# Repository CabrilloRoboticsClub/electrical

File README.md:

# MATE ROV Electrical Stack for 2024 ROV Seahawk II

## Overview
This year, we decided to develop a stack of custom boards for the first time. We made this decision to reduce the size and weight of the Seahawk II while also improving overall durability, reliability, and power consumption. In the past, wiring harnesses were a significant point of failure, so we aimed to reduce their use.

## Intorduction

The Seahawk II electrical stack focuses on high integration. We reduced the number of boards to three, which all connect seamlessly. This minimized space requirements. While the R&D expenses for developing these boards were high, the completed stack is incredibly reliable and significantly reduces costs compared to off-the-shelf options.

## For exstive documetaion go to the wiki

https://github.com/CabrilloRoboticsClub/electrical/wiki

### Members of 2024 electrical team:
- Isaac Wax
- Isaac Eda

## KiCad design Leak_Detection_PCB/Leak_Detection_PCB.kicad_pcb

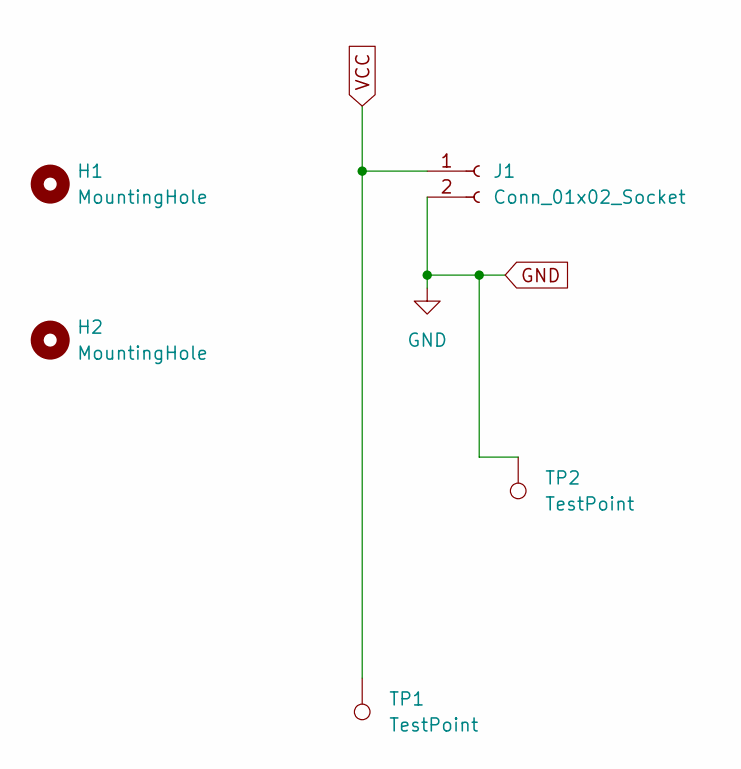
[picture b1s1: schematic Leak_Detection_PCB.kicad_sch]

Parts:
H1, H2: MountingHole; MountingHole_2.2mm_M2_Pad
J1: Conn_01x02_Socket; PinHeader_1x02_P2.54mm_Vertical_SMD_Pin1Left
TP1, TP2: TestPoint; TestPoint_Pad_D1.5mm

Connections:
GND: J1.2, TP2.1
VCC: J1.1, TP1.1

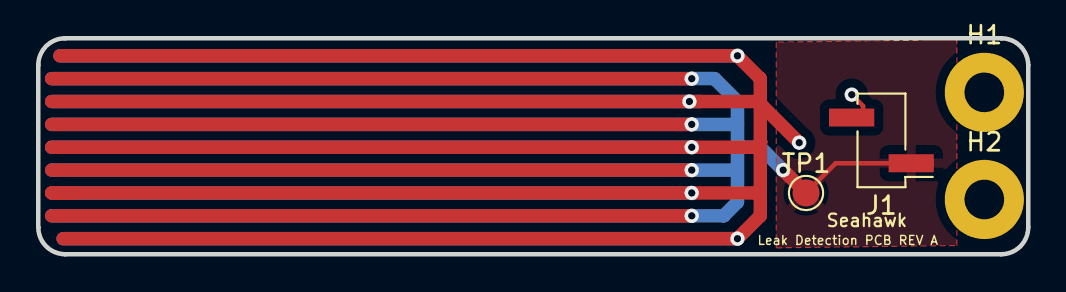
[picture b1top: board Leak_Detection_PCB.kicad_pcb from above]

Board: 2 copper layers, 55.0 x 12.0 mm, 5 parts (1 on the bottom side), 2 nets.

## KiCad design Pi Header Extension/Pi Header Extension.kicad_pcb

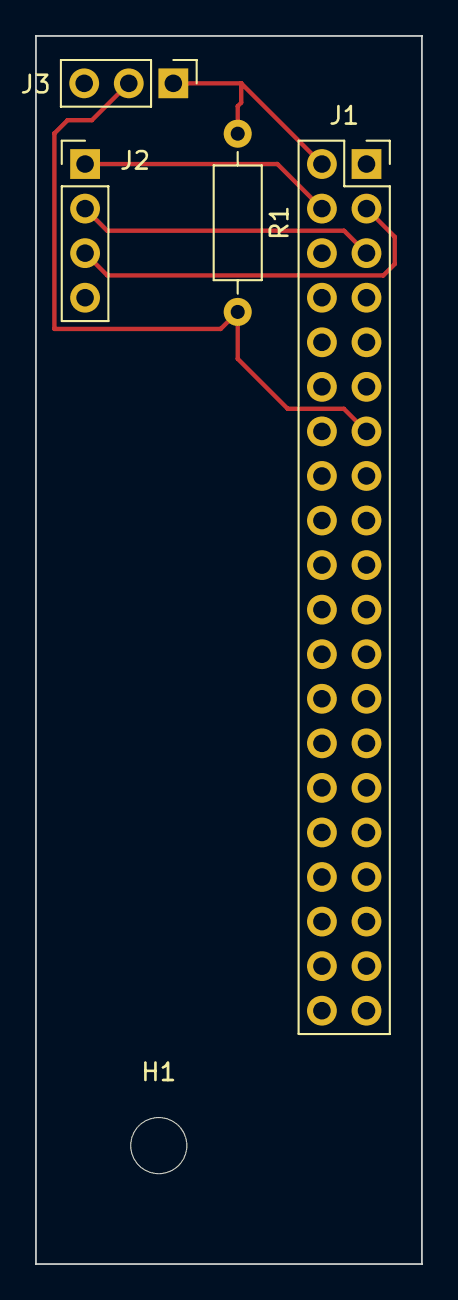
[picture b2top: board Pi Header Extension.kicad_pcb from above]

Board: 2 copper layers, 22.0 x 70.0 mm, 5 parts (0 on the bottom side), 6 nets.

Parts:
H1: MountingHole; MountingHole_3.2mm_M3
J1: Conn_02x20_Odd_Even; PinSocket_2x20_P2.54mm_Vertical
J2: Conn_01x04_Pin; PinHeader_1x04_P2.54mm_Vertical
J3: Conn_01x03_Pin; PinHeader_1x03_P2.54mm_Vertical
R1: 4.7k; R_Axial_DIN0207_L6.3mm_D2.5mm_P10.16mm_Horizontal

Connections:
/5V: J1.2, J3.1, R1.1
/GND: J1.6, J1.14, J2.4, J3.3
/GPIO: J1.13, J3.2, R1.2
/SCL: J1.5, J2.2
/SDA: J1.3, J2.3
/Vin: J1.4, J2.1

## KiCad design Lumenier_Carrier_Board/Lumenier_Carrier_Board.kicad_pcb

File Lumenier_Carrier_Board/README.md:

# Lumenier ESC Carrier Board
https://github.com/CabrilloRoboticsClub/electrical/wiki/ESC-Carrier-Board

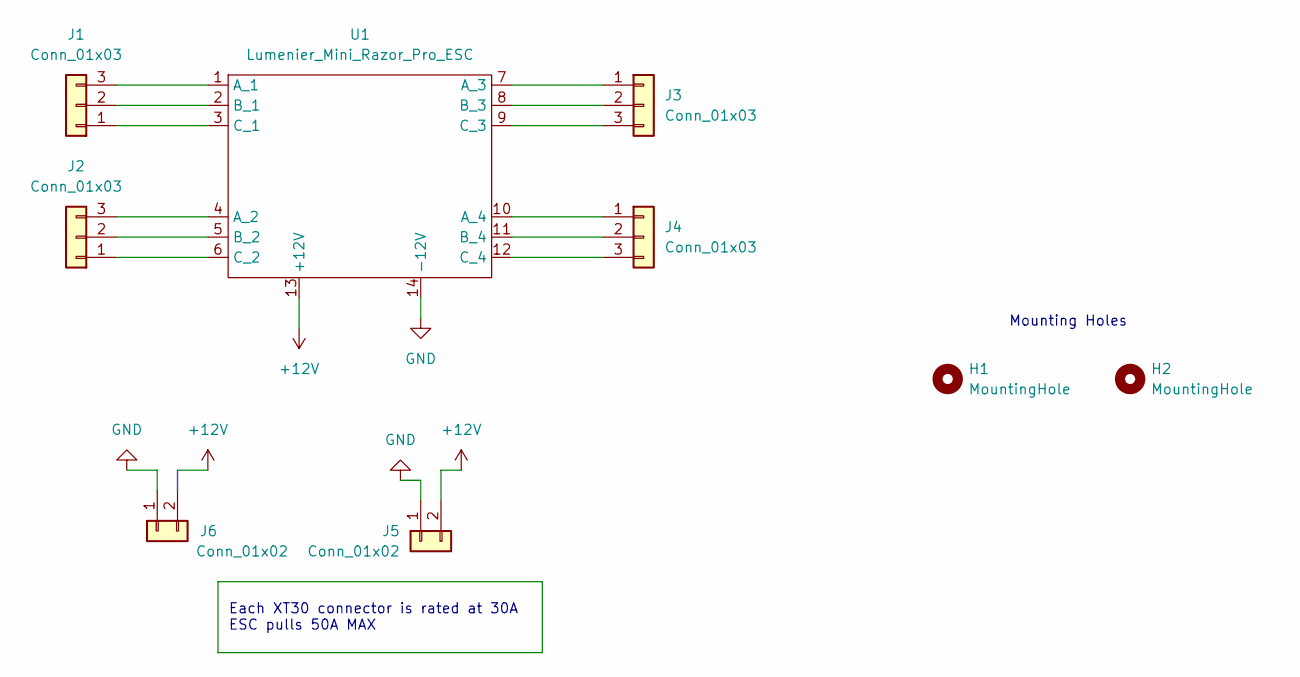
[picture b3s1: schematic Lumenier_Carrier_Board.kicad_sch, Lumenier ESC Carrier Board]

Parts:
H1, H2: MountingHole; MountingHole_3.2mm_M3_ISO14580_Pad
J1, J2, J3, J4: Conn_01x03; AMASS_MR30PW-FB_1x03_P3.50mm_Horizontal
J5, J6: Conn_01x02; AMASS_XT30PW-F_1x02_P2.50mm_Horizontal
U1: Lumenier_Mini_Razor_Pro_ESC

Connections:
+12V: J5.2, J6.2, U1.13 (+12V)
GND: J5.1, J6.1, U1.14 (-12V)
unnamed: J1.1, U1.3 (C_1)
unnamed: J1.2, U1.2 (B_1)
unnamed: J1.3, U1.1 (A_1)
unnamed: J2.1, U1.6 (C_2)
unnamed: J2.2, U1.5 (B_2)
unnamed: J2.3, U1.4 (A_2)
unnamed: J3.1, U1.7 (A_3)
unnamed: J3.2, U1.8 (B_3)
unnamed: J3.3, U1.9 (C_3)
unnamed: J4.1, U1.10 (A_4)
unnamed: J4.2, U1.11 (B_4)
unnamed: J4.3, U1.12 (C_4)

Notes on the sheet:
Mounting Holes
Each XT30 connector is rated at 30A ESC pulls 50A MAX

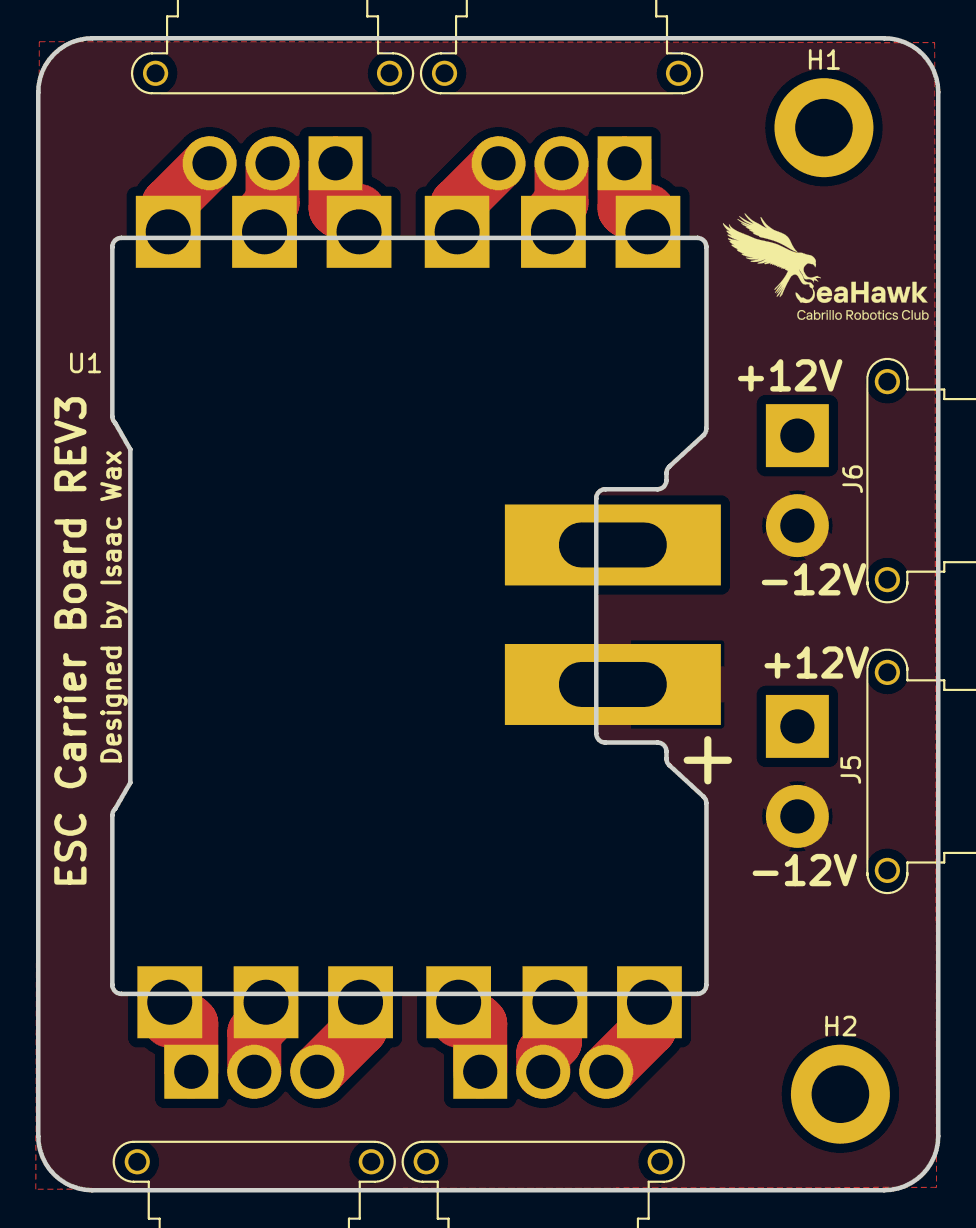
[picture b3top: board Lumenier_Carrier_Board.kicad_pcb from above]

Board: 2 copper layers, 50.0 x 64.0 mm, 9 parts (0 on the bottom side), 14 nets.

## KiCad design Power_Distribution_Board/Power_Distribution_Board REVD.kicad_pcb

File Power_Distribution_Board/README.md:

# Power Distrubtion Board
https://github.com/CabrilloRoboticsClub/electrical/wiki/Power-Distribution-Boad

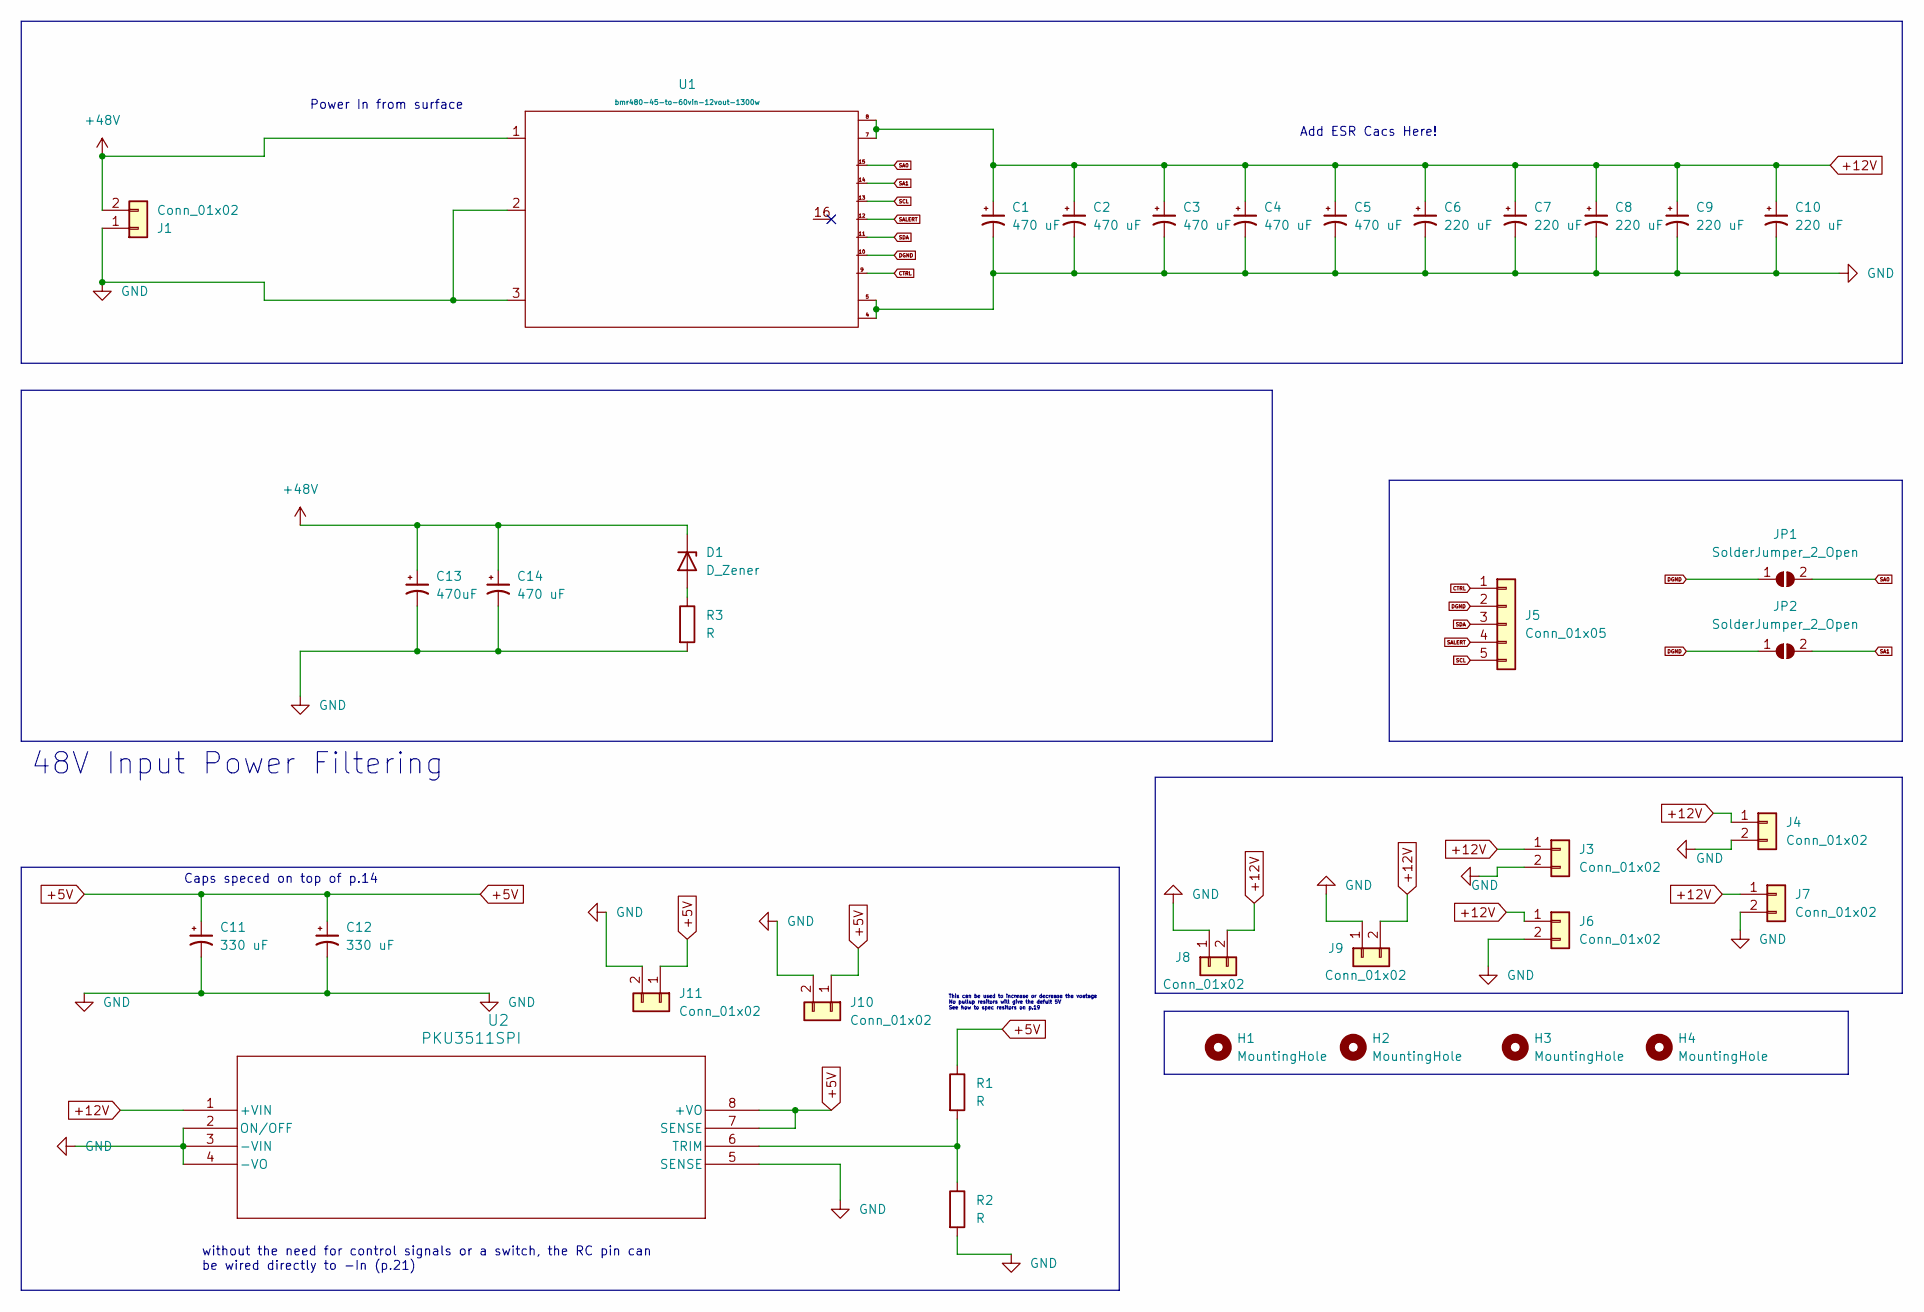
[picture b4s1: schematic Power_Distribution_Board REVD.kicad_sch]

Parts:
C1, C2, C3, C4, C5: 470 uF; CAP_EEHZU1V471V
C6, C7, C8, C9, C10: 220 uF; CAP_EEHZU1H221V
C11, C12: 330 uF; CAP_16SVPG330MX
C13: 470uF; PCAP_16x31.5-THRU-ELECT_NCA
C14: 470 uF; PCAP_16x31.5-THRU-ELECT_NCA
D1: D_Zener; D_DO-41_SOD81_P10.16mm_Horizontal
H1, H2, H3, H4: MountingHole; MountingHole_3.2mm_M3_DIN965_Pad
J1: Conn_01x02; AMASS_XT60-M_1x02_P7.20mm_Vertical
J3, J4, J6, J7: Conn_01x02; AMASS_XT30PW-M_1x02_P2.50mm_Horizontal
J5: Conn_01x05; Molex_PicoBlade_53047-0510_1x05_P1.25mm_Vertical
J8, J9: Conn_01x02; AMASS_XT30U-F_1x02_P5.0mm_Vertical
J10, J11: Conn_01x02; Molex_KK-396_A-41791-0002_1x02_P3.96mm_Vertical
JP1, JP2: SolderJumper_2_Open; SolderJumper-2_P1.3mm_Open_Pad1.0x1.5mm
R1, R2: R; R_2512_6332Metric_Pad1.40x3.35mm_HandSolder
R3: R; R_Axial_DIN0204_L3.6mm_D1.6mm_P5.08mm_Horizontal
U1: bmr480-45-to-60vin-12vout-1300w
U2: PKU3511SPI; PKU 3500S_FPM

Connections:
+5V: C11.1, C12.1, J10.1, J11.1, R1.1, U2.7 (SENSE), U2.8 (+VO)
+12V: C1.1, C2.1, C3.1, C4.1, C5.1, C6.1, C7.1, C8.1, C9.1, C10.1, J3.1, J4.1, J6.1, J7.1, J8.2, J9.2, U1.7, U1.8, U2.1 (+VIN)
+48V: C13.1, C14.1, D1.1 (K), J1.2, U1.1
CTRL: J5.1, U1.9
DGND: J5.2, JP1.1 (A), JP2.1 (A), U1.10
GND: C1.2, C2.2, C3.2, C4.2, C5.2, C6.2, C7.2, C8.2, C9.2, C10.2, C11.2, C12.2, C13.2, C14.2, J1.1, J3.2, J4.2, J6.2, J7.2, J8.1, J9.1, J10.2, J11.2, R2.2, R3.2, U1.2, U1.3, U1.4, U1.5, U2.2 (ON/OFF), U2.3 (-VIN), U2.4 (-VO), U2.5 (SENSE)
unnamed: D1.2 (A), R3.1
unnamed: R1.2, R2.1, U2.6 (TRIM)
SA0: JP1.2 (B), U1.15
SA1: JP2.2 (B), U1.14
SALERT: J5.4, U1.12
SCL: J5.5, U1.13
SDA: J5.3, U1.11

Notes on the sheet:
Add ESR Cacs Here!
This can be used to increase or decrease the voatage No pullup resitors will give the defult 5V See how to spec resitors on p.19
Caps speced on top of p.14
Power In from surface
48V Input Power Filtering
without the need for control signals or a switch, the RC pin can be wired directly to -In (p.21)

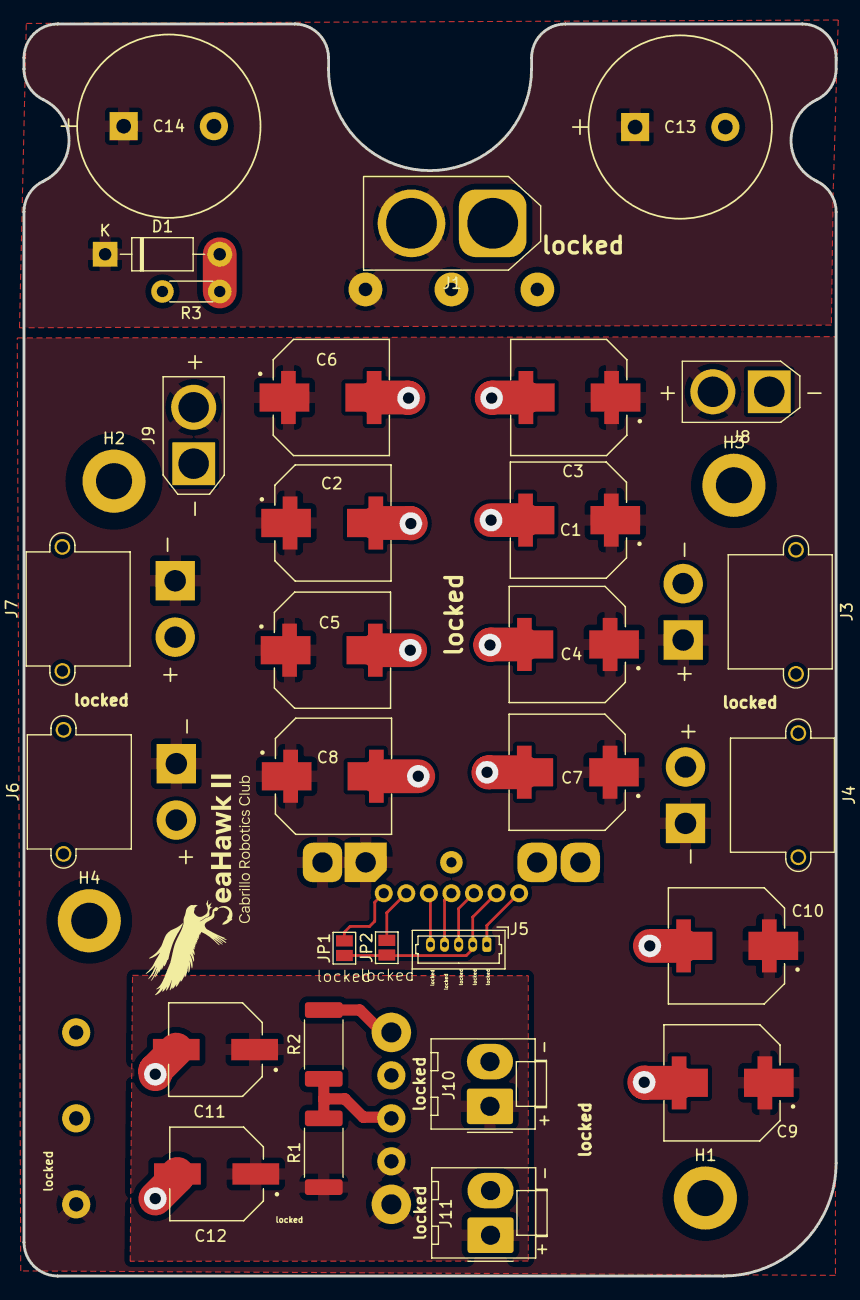
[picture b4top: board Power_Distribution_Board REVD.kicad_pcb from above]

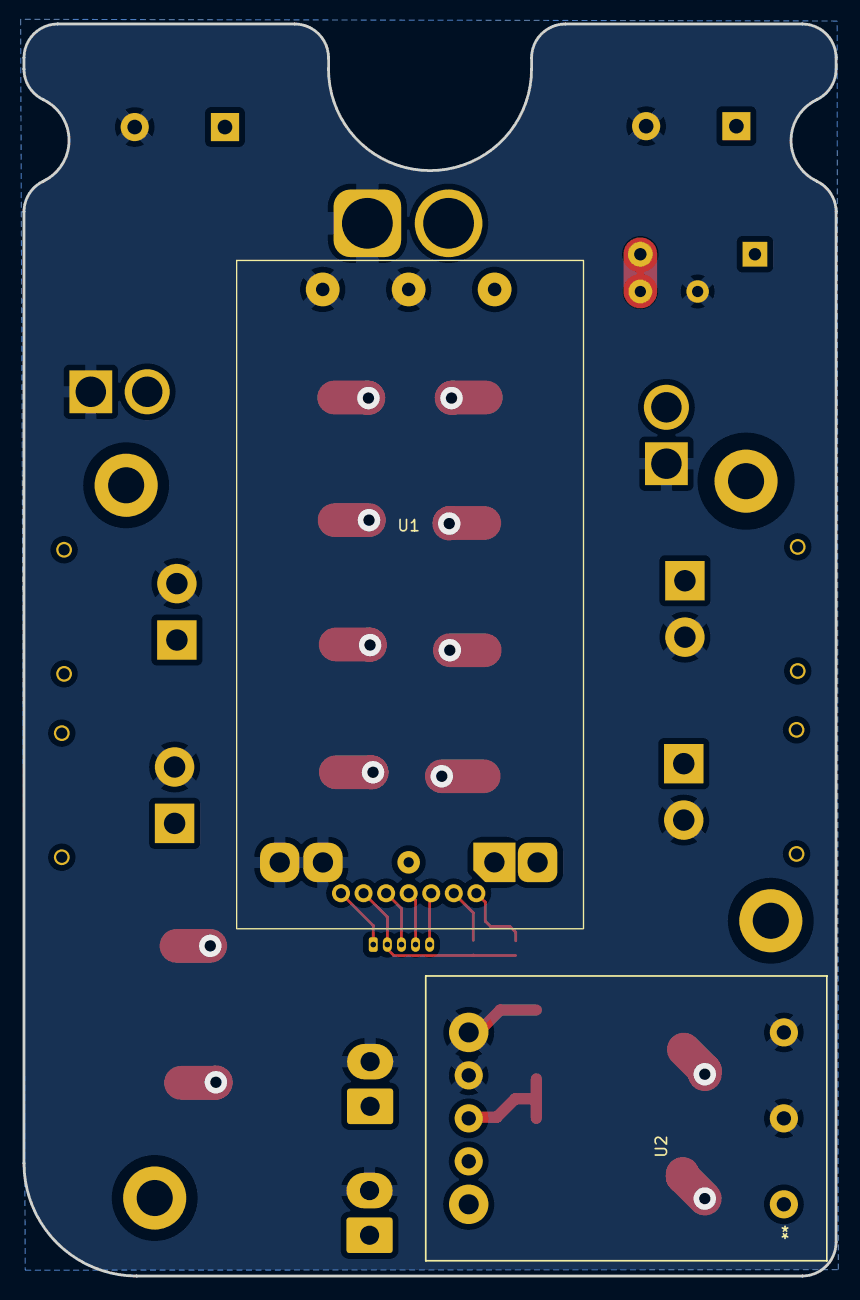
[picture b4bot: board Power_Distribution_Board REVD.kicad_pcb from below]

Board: 2 copper layers, 72.0 x 111.0 mm, 36 parts (2 on the bottom side), 13 nets.

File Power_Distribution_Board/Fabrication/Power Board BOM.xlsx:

Ref | Qnty | Value | Cmp name | Footprint | Description | Vendor | Link | Coust | Total | Orderd
Source: | C:\Users\Isac\Nextcloud\Electrical\E_CAD\Power_Distribution_Board\Power_Distrib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
Date: | 45176.81277777778
Tool: | Eeschema (6.0.5)
Generator: | C:\Program Files\KiCad\6.0\bin\scripting\plugins/bom_csv_grouped_by_value_with_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
C1, C2, C3, C4, C5, | 5.0 | 470 uF | C_Polarized_Small_US | 470UF CAP:CAP_EEHZU1V471V | Polarized capacitor, small US symbol | Mouser | https://www.mouser.com/ProductDetail/Panasonic/EEH-ZU1V471V?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 | 2.5 | 12.5 | 12 arived
 |  |  |  |  |  |  |  |  | 0
C6, C7, C8, C9, C10, | 5.0 | 220 uF | C_Polarized_Small_US | 220UF CAP:CAP_EEHZU1H221V | Polarized capacitor, small US symbol | Mouser | https://www.mouser.com/ProductDetail/Panasonic/EEH-ZU1H221V?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 | 2.5 | 12.5 | 12 arived
 |  |  |  |  |  |  |  |  | 0
C11, C12, | 2.0 | 330 uF | C_Polarized_Small_US | 220UF CAP:CAP_16SVPG330MX | Polarized capacitor, small US symbol | Digkey | https://www.digikey.com/en/products/detail/panasonic-electro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 | 1.73 | 3.46
 |  |  |  |  |  |  |  |  | 0
J1, | 1.0 | Conn_01x02 | Conn_01x02 | Connector_AMASS:AMASS_XT30U-M_1x02_P5.0mm_Vertical | Generic connector, single row, 01x02, script generated (kicad-library-utils/sch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 | Amazon | https://www.amazon.com/Banana-Connector-Upgraded-Battery-Qua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 |  | 10.99 | Arived
 |  |  |  |  |  |  |  |  | 0
J3, J4, J6, J7, J8, J9, | 6.0 | Conn_01x02 | Conn_01x02 | Connector_AMASS:AMASS_XT30PW-M_1x02_P2.50mm_Horizontal | Generic connector, single row, 01x02, script generated (kicad-library-utils/sch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 | Ebay | https://www.amazon.com/gp/product/B099F2PXYN/ref=ppx_yo_dt_b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 | 9.59 | 9.59 | Arived
 |  |  |  |  |  |  |  |  | 0
J5, | 1.0 | Conn_01x05 | Conn_01x05 | Connector_Molex:Molex_PicoBlade_53047-0510_1x05_P1.25mm_Vertical | Generic connector, single row, 01x05, script generated (kicad-library-utils/sch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 | Mouser | https://www.mouser.com/ProductDetail/Molex/53047-0510?qs=KC2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 | 0.39 | 0.39
 |  |  |  |  |  |  |  |  | 0
J10, J11, | 2.0 | Conn_01x02 | Conn_01x02 | Connector_Molex:Molex_KK-396_A-41791-0002_1x02_P3.96mm_Vertical | Generic connector, single row, 01x02, script generated (kicad-library-utils/sch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 | Digkey | https://www.digikey.com/en/products/detail/molex/0009484028/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 | 0.78 | 1.56
 |  |  |  |  |  |  |  |  | 0
R1, R2, | 2.0 | R | R | Resistor_SMD:R_2512_6332Metric_Pad1.40x3.35mm_HandSolder | Resistor | N/A | N/A |  | 0
 |  |  |  |  |  |  |  |  | 0
U1, | 1.0 | BMR4800102/002 | BMR4800102/002 | Power Bricks:bmr480-45-to-60vin-12vout-900w |  | Digkey | https://www.digikey.com/en/products/detail/flex-power-module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 | 152.94 | 129.07 | Arived
 |  |  |  |  |  |  |  |  | 0
U2, | 1.0 | PKU3511SPI | PKU3511SPI | Footprints:PKU 3500S_FPM |  | Digkey | https://www.digikey.com/en/products/detail/flex-power-module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 | 56.46 | 56.46
 |  |  |  |  |  |  |  |  | 236.52
PCB Manufacturing Survices | coust | notes
JLC PCB | 18.30 + shipping | 5X, 2oz copper
PCB Way | 56.68 total | 2 oz copper, 5X, any silkscreen coller
Allpcb
bayareacircuits
OSH Park | 53.65 | 2 oz cupper, .8mm +shipping
